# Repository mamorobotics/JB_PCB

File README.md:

# Junction Box PCB for Mamaroneck Robotics

Using KiCAD

Note - some weird things happened with version history, so there's a section of backups from initial development to Jan 2025, which got deleted, and a section of backups, that was added recently (Feb 25 to March 25). 

The last commit that had the older backups was on Jan 23, 2025 (35d8801). The earliest commit that had the newer (moer important) backups was on May 8, 2026 (ca4f12d).

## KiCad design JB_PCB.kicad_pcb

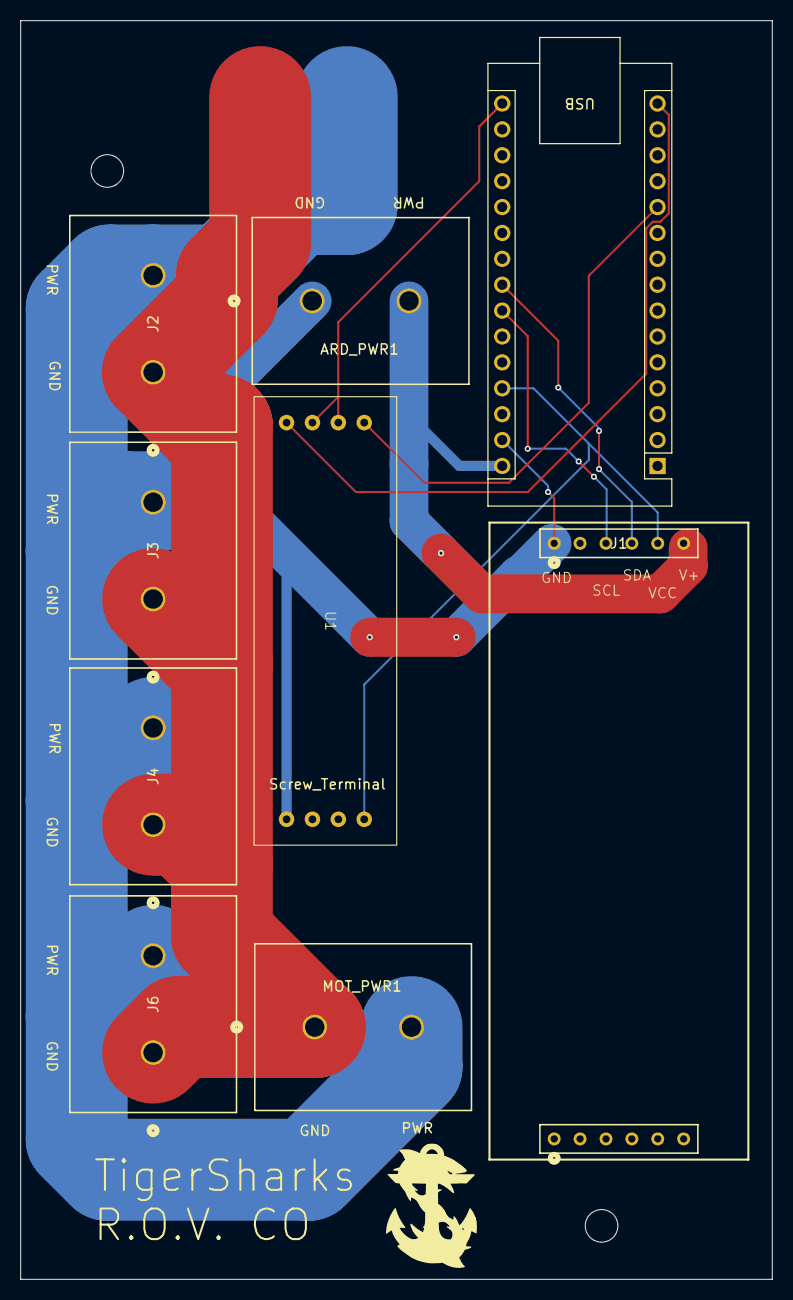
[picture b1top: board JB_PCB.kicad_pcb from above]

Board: 2 copper layers, 73.8 x 123.5 mm, 9 parts (0 on the bottom side), 9 nets.

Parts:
A1: Arduino_Nano_v3.x; Arduino_Nano
ARD_PWR1: Screw_Terminal_01x02; Barrier 2x2
J1: Conn_01x06_Pin; 1x6Headers
J2, J3, J4, J6: Screw_Terminal_01x02; Barrier 2x2
MOT_PWR1: Screw_Terminal_01x02; Barrier 2x2
U1: RS485_Board

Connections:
unnamed: A1.23 (A4), J1.4
unnamed: A1.24 (A5), J1.3
unnamed: A1.11 (D8), U1.RO
unnamed: A1.15 (D12), U1.DI
unnamed: A1.16 (D13), U1.DE, U1.RE
unnamed: A1.27 (+5V), A1.30 (VIN), ARD_PWR1.2, J1.5, J1.6, U1.VCC
unnamed: A1.29 (GND), ARD_PWR1.1, J1.1, U1.GND
unnamed: J2.1, J3.1, J4.1, J6.1, MOT_PWR1.1
unnamed: J2.2, J3.2, J4.2, J6.2, MOT_PWR1.2

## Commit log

2024-11-16 init commit
2024-11-17 gbr Gen
2024-11-22 Added Servo pins
2024-12-07 thickened traces
2025-01-23 added pins for external PWM board
2026-05-08 changes from my laptop from last year
2026-05-09 Add Readme
